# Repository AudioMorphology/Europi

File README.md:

# Europi

## Overview

The Europi is a 16hp Eurorack format sequencer powered by the Raspberry Pi single board computer. It is a digital sequencer that outputs Control Voltages (CV), Modulation and Gate signals, and can be controlled by a variety of signal sources including its own internal clock, external clocks, rotary encoders, MIDI sources and the like.

Europi has been designed to be modular and expandable. The main Europi module, which interfaces directly with the Raspberry Pi has the following features:

* 320 x 240 pixel 16-bit colour touchscreen display
* Continuous rotary push-button encoder
* 4 x tactile 'soft' buttons
* 2 x 1 v/Oct CV output (16-Bit resolution over a 10 volt range)
* 2 x Modulation outputs (16-Bit resolution over a 10 volt range)
* 2 x Gate ouputs (+5 volt leading-edge triggered)
* Clock Out
* Clock In
* Step 1 Out
* Reset In
* Hold In

The primary Europi module interfaces with a number of secondary modules.

The 6hp Europi Minion extends the output capabilities of the Europi by providing an additional 4 x CV and 4 x Gate outputs. Up to 8 Minions can be daisy-chained together so that, including the main Europi module, a complete system can support 34 x CV and 34 x Gate outputs.

The Europi MIDI Minion adds MIDI In, Out and Thru capability and can be used as a means of note entry, as a Clock source and also as a MIDI output. Up to 8 MIDI Minions can be connected to a Europi.

The intention is that, being open sourced, the initial hardware platform could be extended to include support for additional modules, control surfaces and such like, either by using the existing I2C bus that links the Europi to the Minions, or leveraging the USB capabilities of the Raspberry Pi.

## Open Source Hardware Certification

Europi Hardware is certified under the Open Source Hardware Certification Program. Certification Number UK000002

## Interfaces

The Europi is not an analogue sequencer, it is a digital sequencer that outputs analogue CV, Mod and Gate signals. Due to its digital nature the CV outputs are not infinitely variable, but are converted from digital to analogue using 16-Bit Digital to Analogue Converters  (DACs). This gives a resolution of around 6,000 discrete steps per octave over a 10 volt range, ie 500 per semitone. So, whilst the CV outputs are not continuously variable as in a true Analogue sequencer, the resolution is sufficiently high such that the difference isn't discernable in the vast majority of applications.

The output of the DACs have a full-scale output range of 0 to approx 5 volts. In reality, due to manufacturing tolerances, these outputs rarely reach a true zero and often have a minimum achievable output of around 20mv, so the DAC outputs are buffered via Op Amps that are biased with a slight negative voltage, and have an amplification factor of around 2.5 thus a true zero and full-scale 10v output can be set in software, which removes the need for complex and fiddly trimmer potentiometers.

The resistors biasing this output buffer circuit could be selected so that the output swings between, say +/-5v instead of the usual 0-10v, which would then be suitable for use as an audio output (via suitable drivers).

The CV and Gate outputs are connected to the Raspberry Pi using the main user Inter-Integrated Circuit (I2C) bus. The Raspberry Pi actually has two I2C busses, though the first (I2C-0) is generally reserved for querying 'hats' - add-on boards that sit on top of the Pi. The I2C bus is the slower of the Pi's two busses, but is the more flexible and extensible of the two. The faster SPI bus is used for the LCD display and its associated touchscreen interface. 

It is the I2C bus that is used to daisy-chain the various Minions to the main Europi. The I2C Bus is driven at 400KHz

The soft buttons, push-button rotary encoder, and external clock and reset inputs are connected to GPIO pins of the Raspberry Pi via suitable interface circuitry which provides over- and reverse-voltage protection.

Future expansion plans include a CV & Gate Input Minion for driving the Europi from External CV/Gate sources, a gesture-based controller, and a USB & HDMI Minion that connects the Raspberry Pi's USB output to a 2-Port Powered USB Hub, and brings the HDMI output through to a Eurorack panel. The latter is intended to make it simpler to pogram the Europi in situ, and opens the possibility for the connection of other control surfaces via USB.  

## Language and environment

Europi is written in C as it is fairly efficient and links directly with the PIGPIO library (see below). System and operational states are held in global variables. Opinions are divided over the use of global variables in C, though our view is that in a monolithic application such as this, global variables are both quick & efficient (less stack overheads) and simple to understand.

The GUI has been developed using Raylib (http://www.raylib.com), a free Open Source graphics library.

Touchscreen Input is interpreted by RayLib and mapped to Mouse Movements using the ts_uinput daemon, part of TSLIB.

## Principle of operation

Europi makes extensive use of the excellent PIGPIO library (https://github.com/joan2937/pigpio), in particular the I2C functions, PWM functions, and alert functions.

The main Internal clock is generated by establishing a PWM output on GPIO pin 18 (physical pin 12) against which a Callback function is registered. This callback function is therefore called each time the PWM output changes state. An internal counter divides this clock by 96 to give an internal resolution of 96 pulses per quarter note PPQN.

Due to the nature of the PIGPIO library, the PWM frequency can only be set to an integer number of cycles per second (Hz) and given the internal 96PPQN division, a range of typical BPM frequencies can be obtained using the following formula: BPM = (PWM/48)/60. So, for example, a PWM frequency of 200Hz will yield a corresponding BPM of 250 201Hz will yield 251.25 Etc. Obviously therefore, some BPM values cannot be realised using the internal clock due to this integer Hz limitation.

Using the external clock is a different matter as, presumably, an external oscillator can be set to any fractional frequency. The external clock is treated similarly to the internal clock - an alert function is registered against the GPIO pin to which it is applied (GPIO pin 12 Physical pin 32) and this is therefore called each time the external clock changes state. 

The MIDI Minion can alo be used as a clock source at the normal speed of 24 PPQN. 

Within the main body of the code, various control flags and counters are used to record the current operational state, internal vs external clock etc.

The main sequencer object is held in a single global structure called, understandably enough, Europi. Yes, this structure is inefficient. Yes, it would have saved space to malloc structures on the fly at startup, but  statically-defined structure such as this is easy to understand, and memory is not particularly at a premium in the Raspberry Pi.

The GUI has been developed using the Raylib graphics library (http://www.raylib.com). This was originally developed for games programming, but its 2D and text-handling elements are ideally suited to simple GUI development.

Although the Raspberry Pi can be configured to expose a TFT screen as a secondary framebuffer, it doesn't support hardware graphics acceleration when writing to it. I therefore chose to use Raylib to write to the default framebuffer /dev/fb0 and to use the free open source utility raspbi2fb (https://github.com/AndrewFromMelbourne/raspi2fb) to mirror /dev/fb0 to /dev/fb1 as this actually gives better graphic performance than writing directly to /dev/fb1

## Setup and Configuration

As always with Eurorack modules, care must be taken when attaching the module to a Eurorack PSU. We have included reverse-protection diodes to protect against inadvertent reversal of the supply connector, and also +12v and -12v marks are included on the silk screen to try and prevent errors. We have adopted the Doepfer 'standard' keyed shrouded header type of connector to also minimise potential errors.

Up to 8 Minions can be daisy-chained to a single Europi. There are two 6-way Minion connection headers on the main Europi board, one each side to make it easier to place the Minions to the left or right (or both) of the main Europi module. Minions can be daisy-chained in any order, the only stipulation being that each must be given a unique address on the I2C bus. Failure to do so will lead to unpredictable results.

The minion header mirrors the first 8 pins of the Raspberry Pi, so Minions can be connected using straight-through 8-way ribbon cables. Care must be taken to make sure Pin 1 is connected to Pin 1 etc.

As the Minion header mirrors the first 8 pins of the Raspberry Pi header, Minions can be connected directly to a Raspberry Pi without the need to include a Europi module, though obviously all of the functionality of the Europi would be missing from such a configuration (touchscreen LCD, rotary encoder etc) though it does represent a cheaper and simpler entry route into the realm of the Europi.

The Minion address is set using a 3-way DIP switch, using standard binary addressing: 000, 001, 010 .... 111 The address is read by the Minion when power is applied, so a Minion's address should never be changed whilst power is connected.

The MIDI Minion uses 2 separate jumpers to set one of 4 possible addresses, so 4 MIDI Minions can be connected to a Europi.

During startup, the Europi will scan the I2C bus looking for attached Minions, and will assign blocks of 4 Tracks to each Minion as it finds them. I2C address scanning starts from 000 so the Minion with the lowest address will be found first, and the highest last. Minion addresses do not have to be consecutive, just unique.

For ease of use, it would seem to make sense to assign Minion addresses in ascending order from left to right, though it's entirely up to you. During startup, the Europi will briefly flash all the Gate LEDs in the order it found them, which provides a useful indicator as to whether all Minions are in the correct order.

The second stage of the configuration is to set the Zero and Full scale levels for each CV output (both Europi and Minions). This only ever needs to be carried out once, or if the number or order of Minions is changed.

## Pi Configuration and Build Notes

These have been moved to the Wiki

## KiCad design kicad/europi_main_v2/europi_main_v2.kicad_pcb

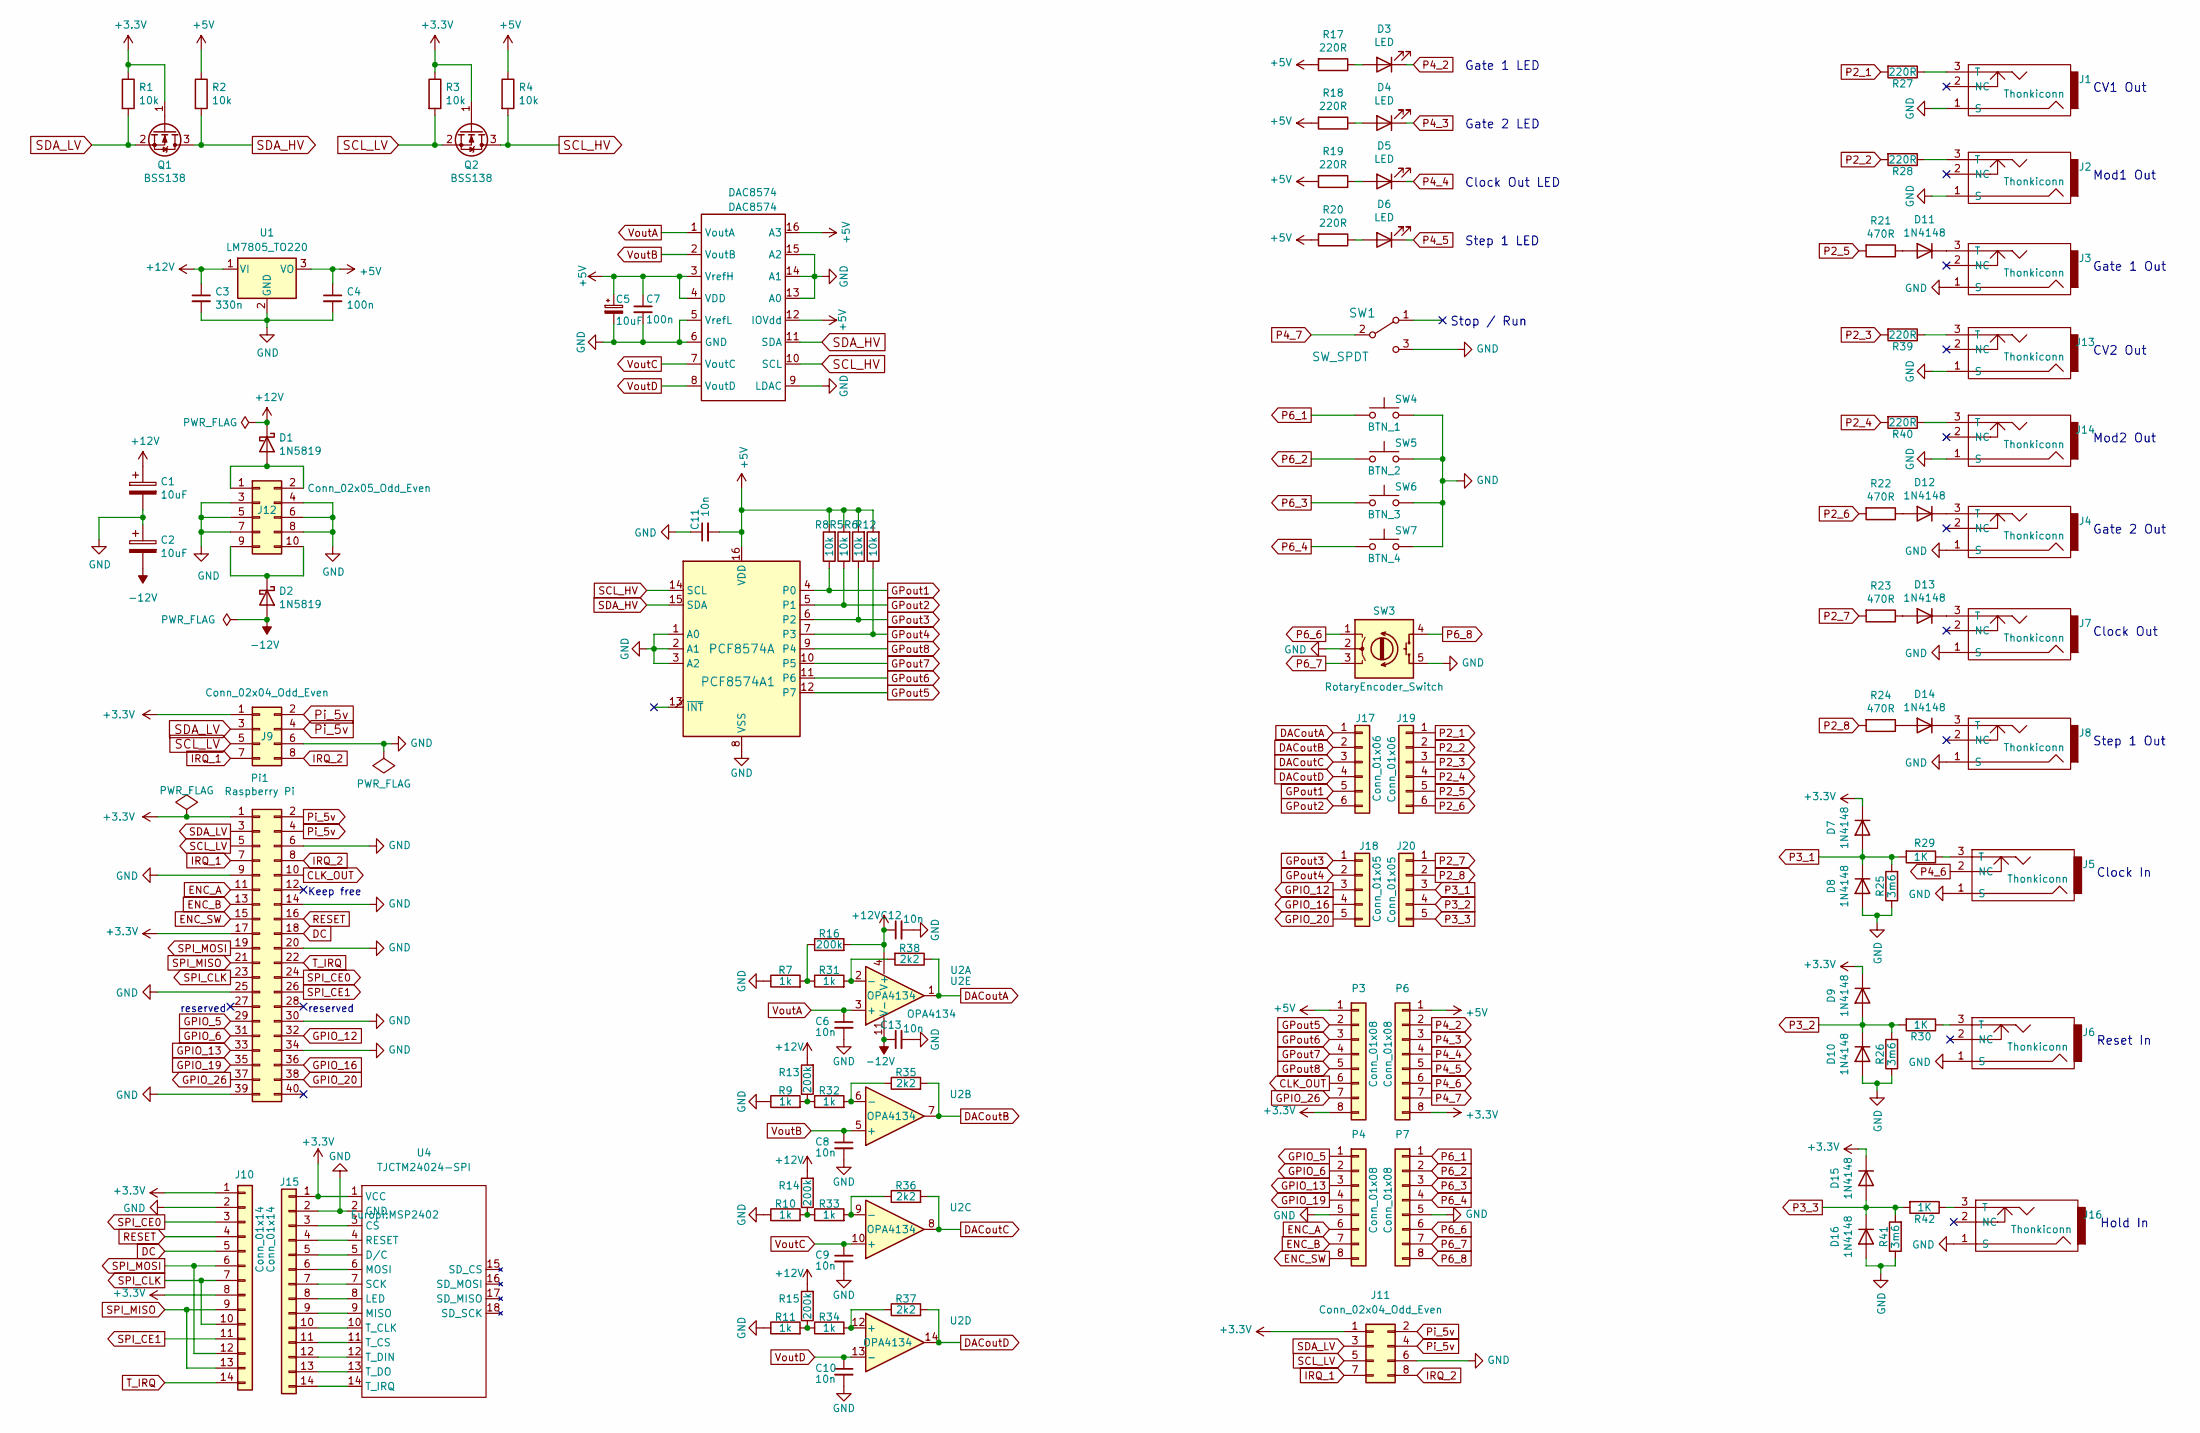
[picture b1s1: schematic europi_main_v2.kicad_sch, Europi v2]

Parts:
C1, C2, C5: 10uF; CP_Radial_D5.0mm_P2.00mm
C3: 330n; tantalum_capacitor
C4, C7: 100n; tantalum_capacitor
C6, C8, C9, C10, C11, C12, C13: 10n; C_0805_2012Metric_Pad1.15x1.40mm_HandSolder
D1, D2: 1N5819; D_DO-41_SOD81_P10.16mm_Horizontal
D3, D4, D5, D6: LED; LED_D3.0mm
D7, D8, D9, D10, D11, D12, D13, D14, D15, D16: 1N4148; D_SOD-123
DAC8574: DAC8574; TSSOP-16_4.4x5mm_P0.65mm
J1, J2, J3, J4, J5, J6, J7, J8, J13, J14, J16: Thonkiconn
J9, J11: Conn_02x04_Odd_Even; PinHeader_2x04_P2.54mm_Vertical
J10, J15: Conn_01x14; PinHeader_1x14_P2.54mm_Vertical
J12: Conn_02x05_Odd_Even; PinHeader_2x05_P2.54mm_Vertical
J17, J19: Conn_01x06; PinHeader_1x06_P2.54mm_Vertical
J18, J20: Conn_01x05; PinHeader_1x05_P2.54mm_Vertical
P3, P4, P6, P7: Conn_01x08; PinHeader_1x08_P2.54mm_Vertical
PCF8574A1: PCF8574A; SOIC-16W_7.5x10.3mm_P1.27mm
Pi1: Raspberry Pi; Raspberry_Pi_Zero_Socketed
Q1, Q2: BSS138; SOT-23
R1, R2, R3, R4, R5, R6, R8, R12: 10k; R_0805_2012Metric_Pad1.15x1.40mm_HandSolder
R7, R9, R10, R11, R31, R32, R33, R34: 1k; R_0805_2012Metric_Pad1.15x1.40mm_HandSolder
R13, R14, R15, R16: 200k; R_0805_2012Metric_Pad1.15x1.40mm_HandSolder
R17, R18, R19, R20, R27, R28, R39, R40: 220R; R_0805_2012Metric_Pad1.15x1.40mm_HandSolder
R21, R22, R23, R24: 470R; R_0805_2012Metric_Pad1.15x1.40mm_HandSolder
R25, R26, R41: 3m6; R_0805_2012Metric_Pad1.15x1.40mm_HandSolder
R29, R30, R42: 1K; R_0805_2012Metric_Pad1.15x1.40mm_HandSolder
R35, R36, R37, R38: 2k2; R_0805_2012Metric_Pad1.15x1.40mm_HandSolder
SW1: SW_SPDT; SPDT_Switch
SW3: RotaryEncoder_Switch; Rotary_encoder_sw_concise
SW4: BTN_1; SW_PUSH_6mm
SW5: BTN_2; SW_PUSH_6mm
SW6: BTN_3; SW_PUSH_6mm
SW7: BTN_4; SW_PUSH_6mm
U1: LM7805_TO220; TO-220-3_Vertical
U2: OPA4134; SOIC-14_3.9x8.7mm_P1.27mm
U4: TJCTM24024-SPI; MSP2402

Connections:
+3V3: D7.1 (K), D9.1 (K), D15.1 (K), J9.1, J10.1, J10.8, J11.1, J15.1, P3.8, P6.8, Pi1.1, Pi1.17, Q1.1 (G), Q2.1 (G), R1.1, R3.1, U4.1 (VCC)
+5V: C4.1, C5.1, C7.1, C11.2, DAC8574.3 (VrefH), DAC8574.4 (VDD), DAC8574.12 (IOVdd), DAC8574.16 (A3), P3.1, P6.1, PCF8574A1.16 (VDD), R2.1, R4.1, R5.2, R6.2, R8.2, R12.2, R17.2, R18.2, R19.2, R20.2, U1.3 (VO); also elsewhere on the board
+12V: C1.1, C3.1, C12.1, D1.1 (K), R13.2, R14.2, R15.2, R16.2, U1.1 (VI), U2.4 (V+); also elsewhere on the board
-12V: C2.2, C13.1, D2.2 (A), U2.11 (V-); also elsewhere on the board
CLK_OUT: P3.6, Pi1.10
DACoutA: J17.1, R38.1, U2.1; also elsewhere on the board
DACoutB: J17.2, R35.2, U2.7; also elsewhere on the board
DACoutC: J17.3, R36.2, U2.8; also elsewhere on the board
DACoutD: J17.4, R37.2, U2.14; also elsewhere on the board
DC: J10.5, Pi1.18
ENC_A: P4.6, Pi1.11
ENC_B: P4.7, Pi1.13
ENC_SW: P4.8, Pi1.15
GND: C1.2, C2.1, C3.2, C4.2, C5.2, C6.2, C7.2, C8.2, C9.2, C10.2, C11.1, C12.2, C13.2, D8.2 (A), D10.2 (A), D16.2 (A), DAC8574.5 (VrefL), DAC8574.6 (GND), DAC8574.9 (LDAC), DAC8574.13 (A0), DAC8574.14 (A1), DAC8574.15 (A2), J1.1 (S), J2.1 (S), J3.1 (S), J4.1 (S), J5.1 (S), J6.1 (S), J7.1 (S), J8.1 (S), J9.6, J10.2, J11.6, J12.3, J12.4, J12.5, J12.6, J12.7, J12.8, J13.1 (S), J14.1 (S), J15.2, J16.1 (S), P4.5, P7.5, PCF8574A1.1 (A0), PCF8574A1.2 (A1), PCF8574A1.3 (A2), PCF8574A1.8 (VSS), Pi1.6, Pi1.9, Pi1.14, Pi1.20, Pi1.25, Pi1.30, Pi1.34, Pi1.39, R7.1, R9.1, R10.1, R11.1, R25.1, R26.1, R41.1, SW1.3 (C), SW3.2 (C), SW3.5 (S2), SW4.2, SW5.2, SW6.2, SW7.2, U1.2 (GND), U4.2 (GND); also elsewhere on the board
GPIO_5: P4.1, Pi1.29
GPIO_6: P4.2, Pi1.31
GPIO_12: J18.3, Pi1.32
GPIO_13: P4.3, Pi1.33
GPIO_16: J18.4, Pi1.36
GPIO_19: P4.4, Pi1.35
GPIO_20: J18.5, Pi1.38
GPIO_26: P3.7, Pi1.37
GPout1: J17.5, PCF8574A1.4 (P0), R8.1
GPout2: J17.6, PCF8574A1.5 (P1), R5.1
GPout3: J18.1, PCF8574A1.6 (P2), R6.1
GPout4: J18.2, PCF8574A1.7 (P3), R12.1
GPout5: P3.2, PCF8574A1.12 (P7)
GPout6: P3.3, PCF8574A1.11 (P6)
GPout7: P3.4, PCF8574A1.10 (P5)
GPout8: P3.5, PCF8574A1.9 (P4)
IRQ_1: J9.7, J11.7, Pi1.7
IRQ_2: J9.8, J11.8, Pi1.8
unnamed 32: D1.2 (A), J12.1, J12.2; also elsewhere on the board
unnamed 33: D2.1 (K), J12.9, J12.10; also elsewhere on the board
unnamed: D3.2 (A), R17.1
unnamed: D4.2 (A), R18.1
unnamed: D5.2 (A), R19.1
unnamed: D6.2 (A), R20.1
unnamed: D11.1 (K), J3.3 (T)
unnamed: D11.2 (A), R21.1
unnamed: D12.1 (K), J4.3 (T)
unnamed: D12.2 (A), R22.1
unnamed: D13.1 (K), J7.3 (T)
unnamed: D13.2 (A), R23.1
unnamed: D14.1 (K), J8.3 (T)
unnamed: D14.2 (A), R24.1
unnamed: J1.3 (T), R27.1
unnamed: J2.3 (T), R28.1
unnamed: J5.3 (T), R29.1
unnamed: J6.3 (T), R30.1
unnamed: J13.3 (T), R39.1
unnamed: J14.3 (T), R40.1
unnamed: J15.3, U4.3 (CS)
unnamed: J15.4, U4.4 (RESET)
unnamed: J15.5, U4.5 (D/C)
unnamed: J15.6, U4.6 (MOSI)
unnamed: J15.7, U4.7 (SCK)
unnamed: J15.8, U4.8 (LED)
unnamed: J15.9, U4.9 (MISO)
unnamed: J15.10, U4.10 (T_CLK)
unnamed: J15.11, U4.11 (T_CS)
unnamed: J15.12, U4.12 (T_DIN)
unnamed: J15.13, U4.13 (T_DO)
unnamed: J15.14, U4.14 (T_IRQ)
unnamed: J16.3 (T), R42.1
unnamed: R10.2, R14.1, R33.1
unnamed: R11.2, R15.1, R34.1
unnamed: R9.2, R13.1, R32.1
unnamed: R7.2, R16.1, R31.1
unnamed 69: R31.2, R38.2, U2.2 (-); also elsewhere on the board
unnamed 70: R32.2, R35.1, U2.6 (-); also elsewhere on the board
unnamed 71: R33.2, R36.1, U2.9 (-); also elsewhere on the board
unnamed 72: R34.2, R37.1, U2.12 (+); also elsewhere on the board
P2_1: J19.1, R27.2
P2_2: J19.2, R28.2
P2_3: J19.3, R39.2
P2_4: J19.4, R40.2
P2_5: J19.5, R21.2
P2_6: J19.6, R22.2
P2_7: J20.1, R23.2
P2_8: J20.2, R24.2
P3_1: D7.2 (A), D8.1 (K), J20.3, R25.2, R29.2
P3_2: D9.2 (A), D10.1 (K), J20.4, R26.2, R30.2
P3_3: D15.2 (A), D16.1 (K), J20.5, R41.2, R42.2
P4_2: D3.1 (K), P6.2
P4_3: D4.1 (K), P6.3
P4_4: D5.1 (K), P6.4
P4_5: D6.1 (K), P6.5
P4_6: J5.2 (NC), P6.6
P4_7: P6.7, SW1.2 (B)
P6_1: P7.1, SW4.1
P6_2: P7.2, SW5.1
P6_3: P7.3, SW6.1
P6_4: P7.4, SW7.1
P6_6: P7.6, SW3.1 (A)
P6_7: P7.7, SW3.3 (B)
P6_8: P7.8, SW3.4 (S1)
Pi_5v: J9.2, J9.4, J11.2, J11.4, Pi1.2, Pi1.4
RESET: J10.4, Pi1.16
SCL_HV: DAC8574.10 (SCL), PCF8574A1.14 (SCL), Q2.3 (D), R4.2
SCL_LV: J9.5, J11.5, Pi1.5, Q2.2 (S), R3.2
SDA_HV: DAC8574.11 (SDA), PCF8574A1.15 (SDA), Q1.3 (D), R2.2
SDA_LV: J9.3, J11.3, Pi1.3, Q1.2 (S), R1.2
SPI_CE0: J10.3, Pi1.24
SPI_CE1: J10.11, Pi1.26
SPI_CLK: J10.7, J10.10, Pi1.23
SPI_MISO: J10.9, J10.13, Pi1.21
SPI_MOSI: J10.6, J10.12, Pi1.19
T_IRQ: J10.14, Pi1.22
VoutA: C6.1, DAC8574.1 (VoutA), U2.3 (+); also elsewhere on the board
VoutB: C8.1, DAC8574.2 (VoutB), U2.5 (+); also elsewhere on the board
VoutC: C9.1, DAC8574.7 (VoutC), U2.10 (+); also elsewhere on the board
VoutD: C10.1, DAC8574.8 (VoutD), U2.13 (-); also elsewhere on the board

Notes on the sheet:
reserved
Keep free
Stop / Run
Gate 1 LED
Gate 2 LED
Clock Out LED
Step 1 LED
CV1 Out
Mod1 Out
Gate 1 Out
CV2 Out
Mod2 Out
Gate 2 Out
Clock Out
Step 1 Out
Clock In
Reset In
Hold In

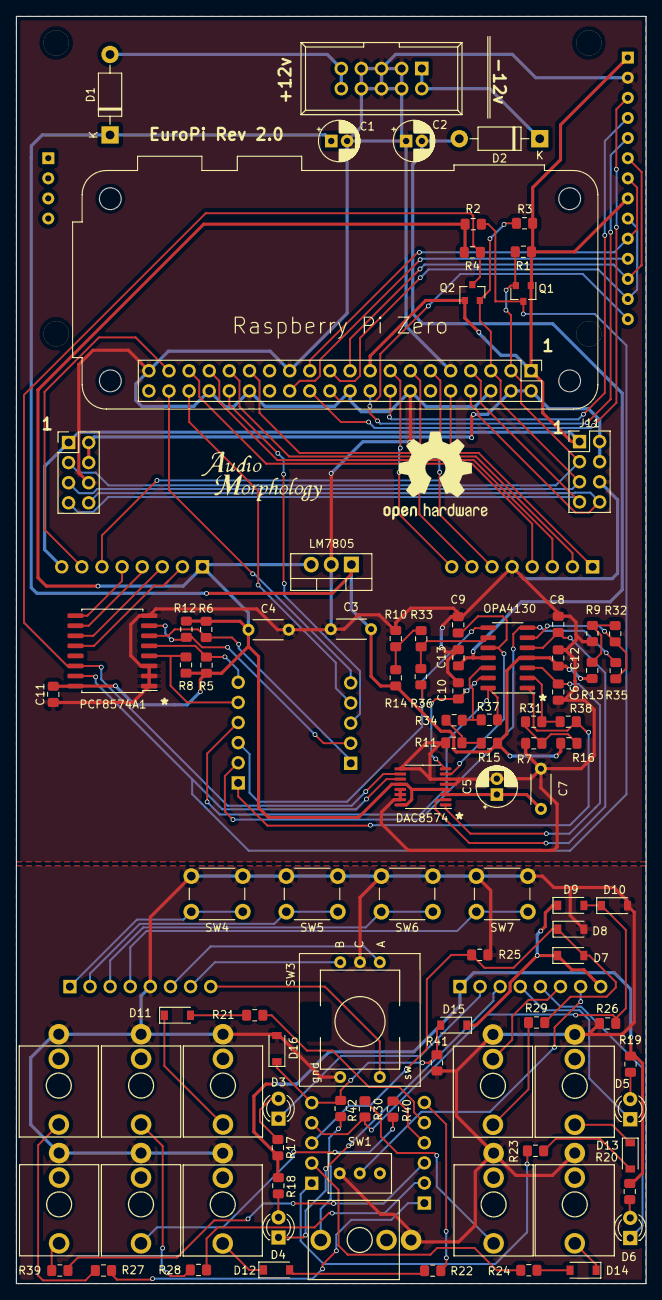
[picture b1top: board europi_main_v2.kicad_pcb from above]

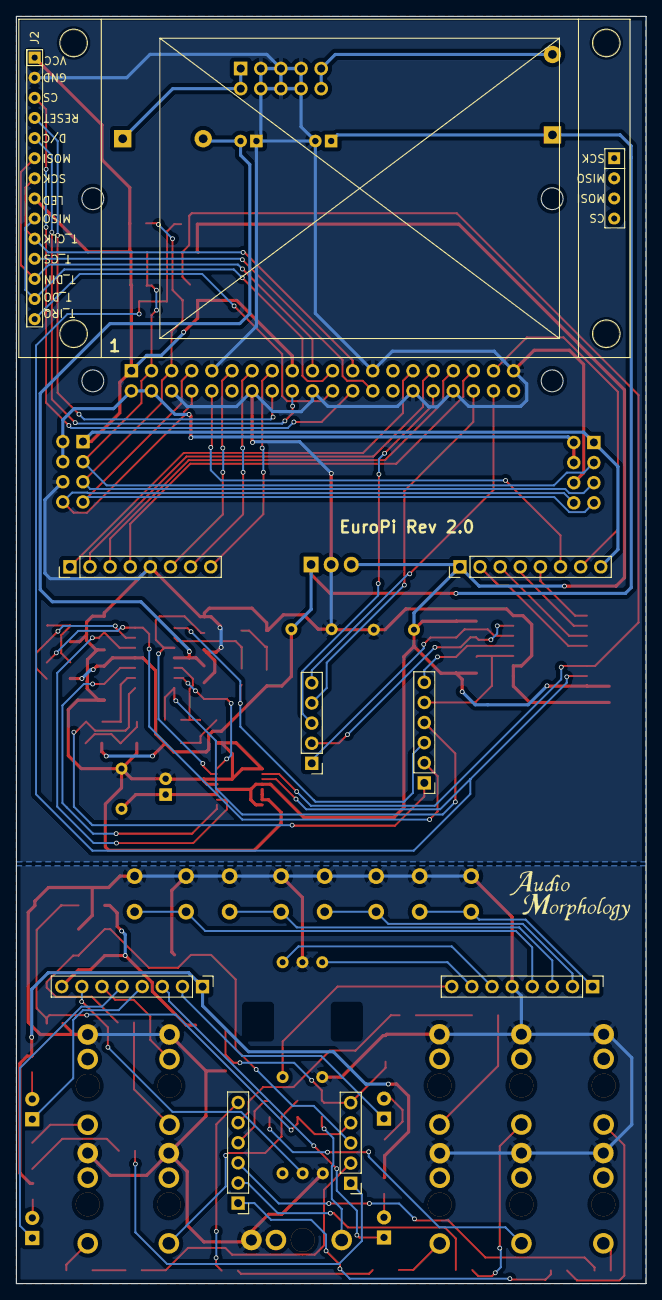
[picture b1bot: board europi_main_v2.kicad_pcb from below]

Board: 2 copper layers, 79.5 x 160.0 mm, 107 parts (9 on the bottom side), 101 nets.

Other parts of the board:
Eurorack1: CONN_02X05; IDC_Header_Straight_10pins
LM7805: LM7805_TO220; TO-220-3_Vertical
OPA4130: OPA4134; SOIC-14_3.9x8.7mm_P1.27mm

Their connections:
+5V: LM7805.3 (VO); also elsewhere on the board
+12V: LM7805.1 (VI), OPA4130.4 (V+); also elsewhere on the board
-12V: OPA4130.11 (V-); also elsewhere on the board
DACoutA: OPA4130.1; also elsewhere on the board
DACoutB: OPA4130.7; also elsewhere on the board
DACoutC: OPA4130.8; also elsewhere on the board
DACoutD: OPA4130.14; also elsewhere on the board
GND: Eurorack1.3, Eurorack1.4, Eurorack1.5, Eurorack1.6, Eurorack1.7, Eurorack1.8, LM7805.2 (GND); also elsewhere on the board
unnamed 32: Eurorack1.9, Eurorack1.10; also elsewhere on the board
unnamed 33: Eurorack1.1, Eurorack1.2; also elsewhere on the board
unnamed 69: OPA4130.2 (-); also elsewhere on the board
unnamed 70: OPA4130.6 (-); also elsewhere on the board
unnamed 71: OPA4130.9 (-); also elsewhere on the board
unnamed 72: OPA4130.12 (+); also elsewhere on the board
VoutA: OPA4130.3 (+); also elsewhere on the board
VoutB: OPA4130.5 (+); also elsewhere on the board
VoutC: OPA4130.10 (+); also elsewhere on the board
VoutD: OPA4130.13 (-); also elsewhere on the board

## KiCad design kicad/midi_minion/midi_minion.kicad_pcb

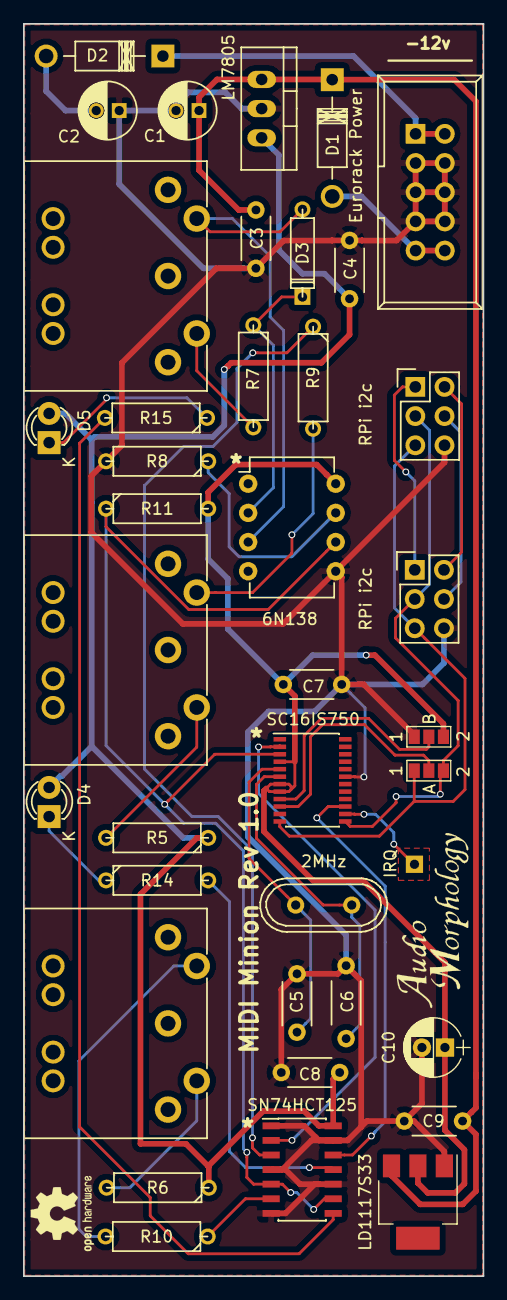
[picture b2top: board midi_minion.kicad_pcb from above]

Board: 2 copper layers, 40.0 x 109.0 mm, 37 parts (0 on the bottom side), 32 nets.

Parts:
2MHz: 2MHz; Crystal_HC49-U_Vertical
6N138: 6N138; DIP-8_W7.62mm
C1, C2: 10uF; C_Radial_D5_L11_P2
C3: 330n; tantalum_capacitor
C4, C9: 100n; tantalum_capacitor
C5: 22pF; tantalum_capacitor
C6: 33pF; disc_capacitor
C7, C8: 100nF; tantalum_capacitor
C10: 10uF; CP_Radial_D5.0mm_P2.00mm
D1, D2: 1N5817; Diode_DO-41_SOD81_Horizontal_RM10
D3: 1N4148; D3
D4, D5: LED; LED-3MM
Eurorack Power: CONN_02X05; IDC_Header_Straight_10pins
IRQ: IRQ; Measurement_Point_Square-TH_Small
LD1117S33: LD1117S33TR; SOT-223
LM7805: RRG7805; 7805
P1: MIDI OUT; SDS-50J
P2: MIDI THRU; SDS-50J
P3: MIDI IN; SDS-50J
R5, R6, R7, R9, R10, R15: 220R; R3-5
R8: 1K; R3-5
R11, R14: 470R; R3-5
RPi i2c, RPi i2c#2: CONN_02X03; Pin_Header_Straight_2x03
SC16IS750: SC16IS750; TSSOP-24_4.4x7.8mm_Pitch0.65mm
SN74HCT125: SN74HCT125; SOIC-14_3.9x8.7mm_Pitch1.27mm

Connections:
+3V3: 6N138.8, C7.1, C10.1, LD1117S33.2, R11.2, SC16IS750.4, SC16IS750.7, SC16IS750.8
+5V: C4.1, C8.2, D4.2, D5.2, LM7805.3, R5.1, R6.1, SN74HCT125.14
+12V: C1.1, C3.1, C9.1, D1.1, LD1117S33.3, LM7805.1
-12V: C2.2, D2.2
GND: 6N138.5, C1.2, C2.1, C3.2, C4.2, C5.2, C6.2, C7.2, C8.1, C9.2, C10.2, Eurorack Power.3, Eurorack Power.4, Eurorack Power.5, Eurorack Power.6, Eurorack Power.7, Eurorack Power.8, LD1117S33.1, LM7805.2, R8.2, RPi i2c.6, RPi i2c#2.6, SC16IS750.19, SN74HCT125.1, SN74HCT125.4, SN74HCT125.7, SN74HCT125.10, SN74HCT125.13
unnamed: 2MHz.1, C5.1, SC16IS750.5
unnamed: 2MHz.2, C6.1, SC16IS750.6
unnamed: D1.2, Eurorack Power.9, Eurorack Power.10
unnamed: D2.1, Eurorack Power.1, Eurorack Power.2
unnamed: 6N138.2, D3.1, R7.1
unnamed: 6N138.3, D3.2, P3.5
unnamed: D4.1, R14.1
unnamed: D5.1, R15.1
unnamed: SC16IS750.2, SN74HCT125.2
unnamed: R9.1, SN74HCT125.3
unnamed: 6N138.6, R11.1, SC16IS750.3, SN74HCT125.5, SN74HCT125.9
unnamed: R10.1, SN74HCT125.6
unnamed: R15.2, SN74HCT125.8
unnamed: R14.2, SN74HCT125.11
unnamed: SC16IS750.15, SN74HCT125.12
unnamed: IRQ.1, SC16IS750.14
unnamed: 6N138.7, R8.1
unnamed: P1.4, R5.2
unnamed: P1.5, R9.2
unnamed: P2.4, R6.2
unnamed: P2.5, R10.2
unnamed: P3.4, R7.2
unnamed: RPi i2c.1, RPi i2c#2.1
unnamed: RPi i2c.2, RPi i2c#2.2
unnamed: RPi i2c.4, RPi i2c#2.4
SCL_LV: RPi i2c.5, RPi i2c#2.5, SC16IS750.12
SDA_LV: RPi i2c.3, RPi i2c#2.3, SC16IS750.13

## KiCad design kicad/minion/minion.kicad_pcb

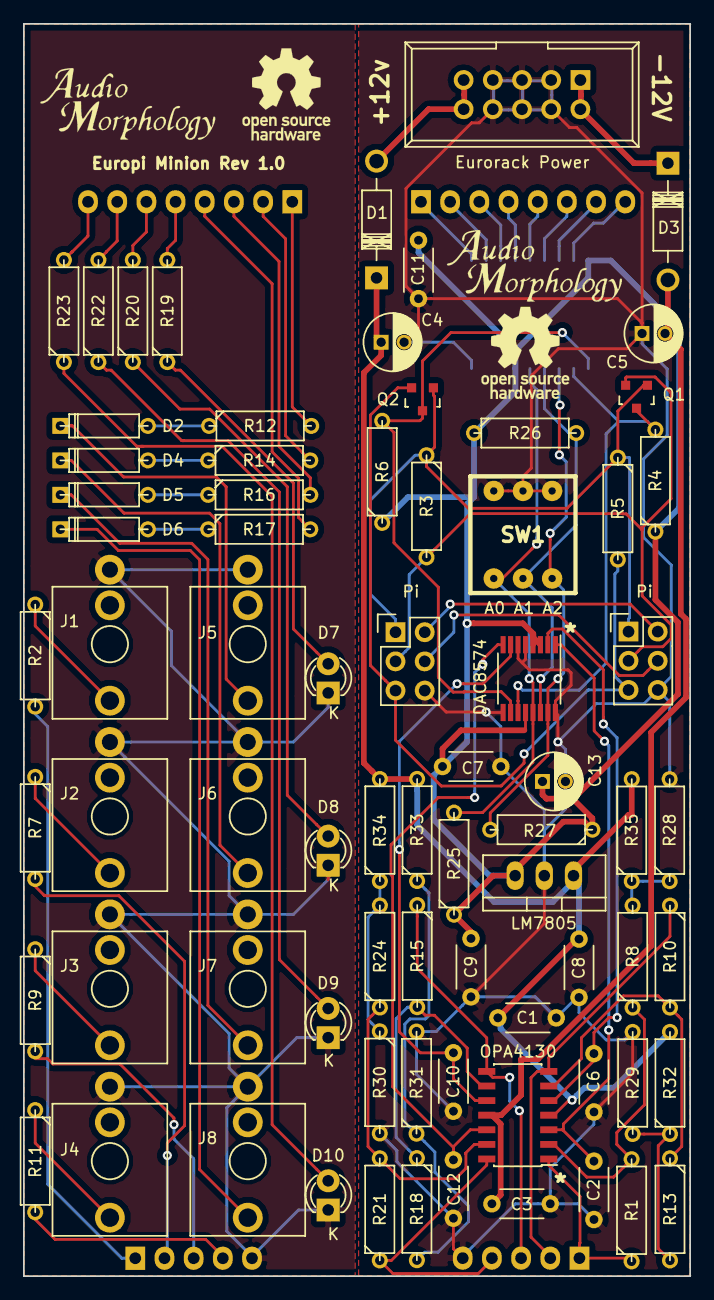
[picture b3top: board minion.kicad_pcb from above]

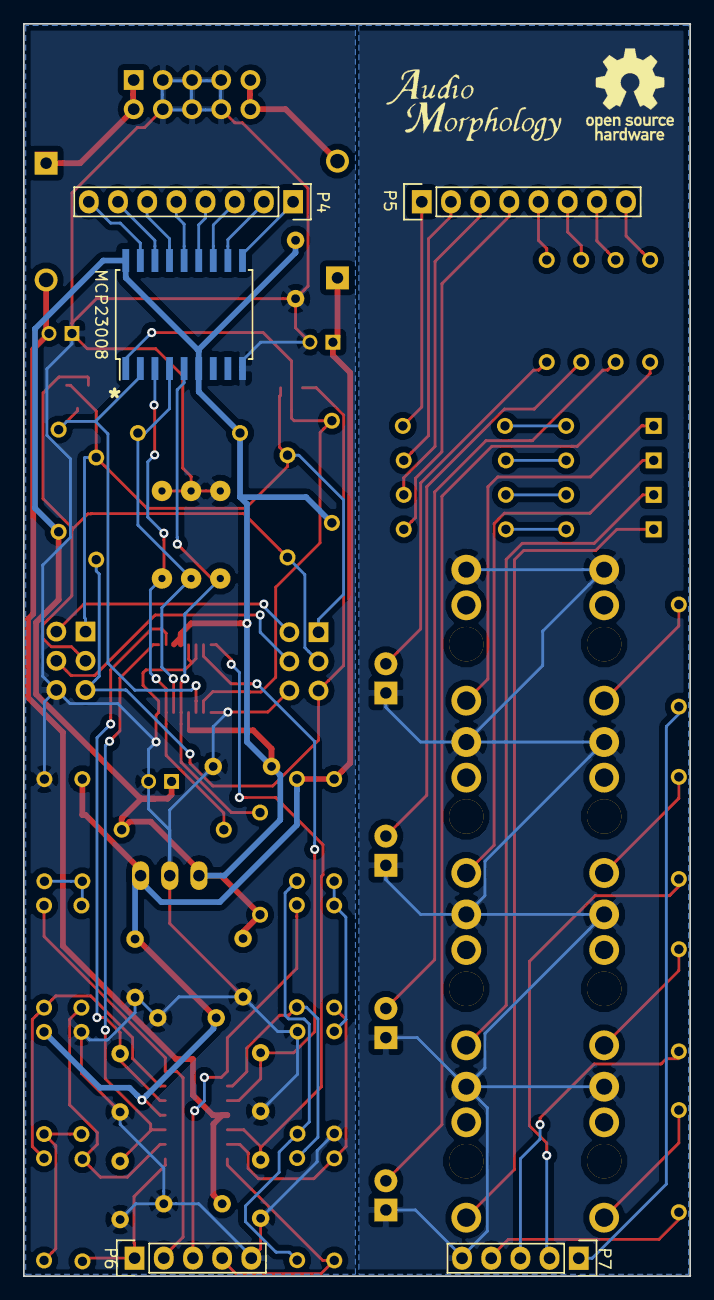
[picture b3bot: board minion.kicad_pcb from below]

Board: 2 copper layers, 58.0 x 109.0 mm, 80 parts (5 on the bottom side), 68 nets.

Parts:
C1, C2, C3, C6, C10, C11, C12: 10n; tantalum_capacitor
C4, C5, C13: 10uF; C_Radial_D5_L11_P2
C7, C9: 100n; tantalum_capacitor
C8: 330n; tantalum_capacitor
D1, D3: 1N5817; Diode_DO-41_SOD81_Horizontal_RM10
D2, D4, D5, D6: 1N4148; D3
D7, D8, D9, D10: LED; LED-3MM
DAC8574: DAC8574; TSSOP-16_4.4x5mm_Pitch0.65mm
Eurorack Power: CONN_02X05; IDC_Header_Straight_10pins
J1, J2, J3, J4, J5, J6, J7, J8: Thonkiconn
LM7805: RRG7805; 7805
MCP23008: MCP23008; SOIC-18_7.5x11.6mm_Pitch1.27mm
OPA4130: OPA4130; SOIC-14_3.9x8.7mm_Pitch1.27mm
P4, P5: CONN_01X08; Pin_Header_Straight_1x08
P6, P7: CONN_01X05; Pin_Header_Straight_1x05
Pi: CONN_02X03; Pin_Header_Straight_2x03
Pi#2: CONN_02X03; Pin_Header_Straight_2x03
Q1, Q2: BSS138; SOT-23
R1, R10, R15, R21: 2k2; R3-5
R2, R7, R9, R11, R19, R20, R22, R23: 220R; R3-5
R3, R4, R5, R6, R8, R13, R18, R24, R25, R26, R27: 10k; R3-5
R12, R14, R16, R17: 470R; R3-5
R28, R29, R30, R31: 1k; R3-5
R32, R33, R34, R35: 200k; R3-5
SW1: DIPS_03; DIPS-DS03

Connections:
+3V3: Pi.1, Pi#2.1, Q1.1, Q2.1, R3.1, R5.1
+5V: C7.1, C9.1, C11.2, C13.1, DAC8574.3, DAC8574.4, DAC8574.12, LM7805.3, MCP23008.6, MCP23008.18, R4.1, R6.1, R25.1, R26.1, R27.1
+12V: C1.2, C4.1, C8.1, D1.1, LM7805.1, OPA4130.4, R32.2, R33.2, R34.2, R35.2
-12V: C3.2, C5.2, D3.2, OPA4130.11
A0: DAC8574.13, MCP23008.5, R25.2, SW1.1
A1: DAC8574.14, MCP23008.4, R26.2, SW1.2
A2: DAC8574.15, MCP23008.3, R27.2, SW1.3
DACin1: P7.1, R2.2
DACin2: P7.2, R7.2
DACin3: P7.3, R9.2
DACin4: P7.4, R11.2
DACout1: OPA4130.1, P6.1, R1.1
DACout2: OPA4130.7, P6.2, R10.1
DACout3: OPA4130.8, P6.3, R15.1
DACout4: OPA4130.14, P6.4, R21.1
GND: C1.1, C2.2, C3.1, C4.2, C5.1, C6.2, C7.2, C8.2, C9.2, C10.2, C11.1, C12.2, C13.2, D7.1, D8.1, D9.1, D10.1, DAC8574.5, DAC8574.6, DAC8574.9, DAC8574.16, Eurorack Power.3, Eurorack Power.4, Eurorack Power.5, Eurorack Power.6, Eurorack Power.7, Eurorack Power.8, J1.1, J2.1, J3.1, J4.1, J5.1, J6.1, J7.1, J8.1, LM7805.2, MCP23008.9, P6.5, P7.5, Pi.6, Pi#2.6, R28.2, R29.2, R30.2, R31.2, SW1.4, SW1.5, SW1.6
GPin1: P5.1, R12.2
GPin2: P5.2, R14.2
GPin3: P5.3, R16.2
GPin4: P5.4, R17.2
GPin5: P5.5, R19.2
GPin6: P5.6, R20.2
GPin7: P5.7, R22.2
GPin8: P5.8, R23.2
GPout1: MCP23008.10, P4.1
GPout2: MCP23008.11, P4.2
GPout3: MCP23008.12, P4.3
GPout4: MCP23008.13, P4.4
GPout5: MCP23008.14, P4.5
GPout6: MCP23008.15, P4.6
GPout7: MCP23008.16, P4.7
GPout8: MCP23008.17, P4.8
unnamed: D1.2, Eurorack Power.9, Eurorack Power.10
unnamed: D2.1, J5.3
unnamed: D2.2, R12.1
unnamed: D3.1, Eurorack Power.1, Eurorack Power.2
unnamed: D4.1, J6.3
unnamed: D4.2, R14.1
unnamed: D5.1, J7.3
unnamed: D5.2, R16.1
unnamed: D6.1, J8.3
unnamed: D6.2, R17.1
unnamed: D7.2, R19.1
unnamed: D8.2, R20.1
unnamed: D9.2, R22.1
unnamed: D10.2, R23.1
unnamed: J1.3, R2.1
unnamed: J2.3, R7.1
unnamed: J3.3, R9.1
unnamed: J4.3, R11.1
unnamed: Pi.2, Pi#2.2
unnamed: Pi.4, Pi#2.4
unnamed: OPA4130.2, R1.2, R8.1
unnamed: OPA4130.6, R10.2, R13.1
unnamed: R13.2, R29.1, R32.1
unnamed: OPA4130.9, R15.2, R18.1
unnamed: R18.2, R31.1, R33.1
unnamed: OPA4130.13, R21.2, R24.1
unnamed: R24.2, R30.1, R34.1
unnamed: R8.2, R28.1, R35.1
SCL_HV: DAC8574.10, MCP23008.1, Q2.3, R6.2
SCL_LV: Pi.5, Pi#2.5, Q2.2, R5.2
SDA_HV: DAC8574.11, MCP23008.2, Q1.3, R4.2
SDA_LV: Pi.3, Pi#2.3, Q1.2, R3.2
VoutA: C2.1, DAC8574.1, OPA4130.3
VoutB: C6.1, DAC8574.2, OPA4130.5
VoutC: C10.1, DAC8574.7, OPA4130.10
VoutD: C12.1, DAC8574.8, OPA4130.12

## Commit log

2016-10-17 Added Kicad project, schematic and PCB files for Europi & Minion, including Frontpanels laid out in Kicad
2016-10-20 Clarify License & attribution
2016-10-23 new file: hardware/bom.ods new file: hardware/pi_header_pinout_assignment.ods
2016-10-23 removed redundant directory
2016-10-23 Added project-specific Kicad library
2016-10-27 modified: europi_func1.c modified: europi_func2.c modified: font_8x16.c modified: font_8x8.c modified: front_panel.c modified: splash.c
2016-10-27 modified: europi_func1.c
2016-11-02 giving up on bit banging
2016-11-02 testing minion
2016-11-02 more robust method for detecting Minions on startup
2016-11-02 removed redundant DAC Finder function
2016-11-07 Update README.md
    Added OSHWA Certification number
2016-11-10 now launching detached threads for handling gates, Triggers and re-trigging
2016-11-12 skeleton code for AD & ADSR ramp shapes
2016-11-13 Adding mutexes to protect MCP23008 channhels
2016-11-23 experimenting with raylib grids
2016-11-27 added bgr=1 argument to fbtft driver config to swap Red & Blue on SpotPear TFT
2016-11-27 new file: build_notes.txt modified: europi.c modified: europi_func1.c
2016-11-27 updated README.md now using Raylib for GUI
2016-11-28 splash screen now loaded as a Texture using Raylib
2016-11-29 start menuing overlays
2016-12-03 basic sub-menu structure working
2016-12-04 Basic menu structure completed
2016-12-05 set zero menu function implemented
2016-12-06 set zero & set 10v config functions working, basic save & load sequences completed
2016-12-08 menu function for setting loop points & initialising a sequence
2016-12-11 quantisation select and step pitch set menu functions
2016-12-18 Prototype single channel view
2017-01-02 Touchscreen mapped to mouse movements via tslib and ts_uinput virtual device
2017-01-09 remove obsolete files
2017-01-11 Updated Pi Header pinouts
2017-01-14 modified: europi.c modified: europi.h modified: europi_func1.c
2017-01-19 added new code module europi_gui.c to keep all the gui routines together
2017-01-24 menus working under touch control
2017-01-28 modified: europi.c modified: europi.h modified: europi_func2.c modified: europi_gui.c
2017-01-28 Added keyboard graphic
2017-01-28 completed first version of on-screen keyboard
2017-01-29 new file: resources/sequences/.gitignore
2017-01-29 Added dialog box texture
2017-01-29 Added text input dialog box
2017-01-29 File Open and File SaveAs dialogs completed
2017-01-29 backing up to Github
2017-01-31 Added soft-button bar graphic
2017-01-31 Updated dialog.png
2017-01-31 Implemented soft-button structure to mimick the physical buttons, so that both behave identically
2017-02-01 Added top bar graphic
2017-02-01 Added main screen image
2017-02-01 re-worked main screen objects, menus etc
2017-02-01 file save as now working
2017-02-02 moved the set loop, scale and pitch functions into the gui
2017-02-04 set pitch moved to new GUI, debug messages can now be directed to TFT screen overlay
2017-02-05 fixed the pitch adjust so it correctly leaps to the next quantised note value
2017-02-05 new file: slew_profiles.h
2017-02-05 update slew_profiles.h
    Changed from Int array to arrays of pre-calculated floats
2017-02-05 modified: europi.c modified: europi.h modified: europi_func1.c modified: europi_func2.c modified: slew_profiles.h
2017-03-28 Started adding MIDI Minion BOM items
2017-03-29 MIDI Minion Rev 1.0 Schematic & Brd files
2017-05-14 Added MIDI Minion finder
2017-06-06 some work on MIDI output messages
2017-06-06 fixed most recent batch of compiler warnings
2017-06-07 Added Track direction (Fwd, Reverse, Pendulum, Random)
2017-06-07 bug fix in Pendulum track direction
2017-06-07 bug fix in MIDI Out
2017-06-07 Implemented External MIDI Clock sync
2017-06-08 experimenting with alternative single channel display paradigms
2017-06-10 Vertical Scrollbar Implementation
2017-06-11 vertical scroll bar on 8x8 Grid layout
2017-06-11 w.i.p. Single Step edit page
2017-06-12 more work on single step edit page
2017-06-13 developing pitch editor using bargraph paradigm
2017-06-14 nightly build
2017-06-15 single channel display
2017-06-22 re-worked [step] structure & ratchetting code
2017-06-23 Implemented Step Repeats
2017-06-23 Added Bjorklund Euclidian tables
2017-06-24 Implemented Euclidian Ratchets
2017-06-25 ratchetting gate display on single track page
2017-06-25 ADSR Profile generator completed
2017-06-27 hardware config changes saved to disk, Modal Dialog implementation, Set zero and Set 10v implemented
2017-07-06 added global tuning flag to force all CV channels to temporarily output the same Raw voltage (Scaled appropriately)
2017-07-10 re-worked & simplified AD & ADSR structures
2017-07-12 tidied up the logged messages in the MinionFinder routines to clarify the i2c addresses that each device is using
2017-07-12 Added basic structure for Single channel AD & ADSR display / edit screen
2017-07-16 Added Log Profiles
2017-07-16 Added reverse Logarithmic profiles
2017-07-16 added Log slew profiles
2017-07-19 Sine & Cosine curves
2017-07-22 slew profiles drawing on SingleAD Screen
2017-10-08 Waft components
2017-12-11 Active Overlays now held in Bit Fields rather than structures
2017-12-13 Fixed screen overlay flags
2017-12-14 touch interface for single step parameters
2017-12-16 more GUI work
2017-12-17 single step GUI completed
2017-12-18 fixed the gesture tap detection
2017-12-19 daily build
2017-12-24 implented short scroll bar for when top menu bar active
2018-01-15 KiCad footprint & 3D Model s uploaded
2018-01-30 Add files via upload
    Updated Europi Library
2021-01-04 Various GUI bug fixes
2021-01-05 Set initial sequence = half way up 4th octave
2021-01-06 Add files via upload
    Small floating dialog
2021-01-06 Overlay Timer thread
2021-01-13 Development of grid view
2021-01-17 Work on Gui_Grid display
2021-01-19 Work on Slew GUI
2021-01-19 Small fix to Slew GUI
2021-01-29 Fixed compiler warnings
2021-03-13 Create test
2021-03-13 Add files via upload
    Europi Version 2 schematic, board and Front Panel
2021-03-13 Add files via upload
    Gerbers for the Europi Main board Version 2
2021-03-13 Create front panel gerbers
2021-03-13 Add files via upload
    Gerbers for the Europi V2 Front Panel
2021-03-23 Starting build against V2 Hardware
2021-03-28 Fixed quant problems on Track 2
2021-03-28 Starting work on Modulation channel threads
2021-04-11 Modulation Thread creation
2021-04-11 Mod Triangle Ramp
2021-04-18 Added per-track clock divisor
2021-07-04 Introducing Swing
2021-10-31 Changed SpriteFont to Font definition
